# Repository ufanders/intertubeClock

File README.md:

# intertubeClock
An ESP32-powered nixie tube clock.
Power supply copied from this Hackaday.io project:
https://hackaday.io/project/27899-nixie-tube-power-supply

Read more about this project on my blog here!: https://www.andersknelson.com/blog/?p=363

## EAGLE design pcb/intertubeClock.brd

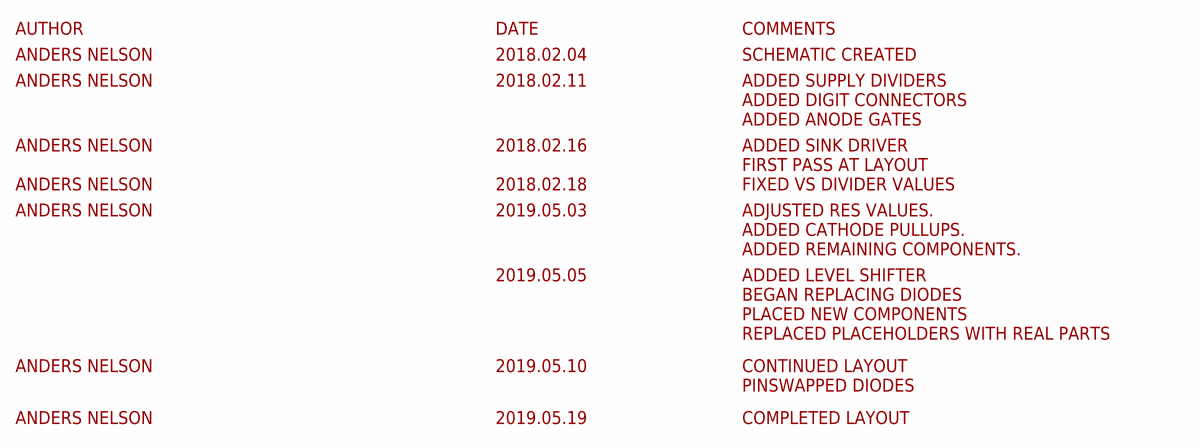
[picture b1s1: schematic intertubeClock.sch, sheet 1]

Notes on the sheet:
AUTHOR
DATE
COMMENTS
ANDERS NELSON
2018.02.04
SCHEMATIC CREATED
2018.02.11
ADDED SUPPLY DIVIDERS ADDED DIGIT CONNECTORS ADDED ANODE GATES
2018.02.16
ADDED SINK DRIVER FIRST PASS AT LAYOUT
FIXED VS DIVIDER VALUES
2019.05.03
2018.02.18
ADJUSTED RES VALUES. ADDED CATHODE PULLUPS. ADDED REMAINING COMPONENTS.
2019.05.05
ADDED LEVEL SHIFTER BEGAN REPLACING DIODES PLACED NEW COMPONENTS REPLACED PLACEHOLDERS WITH REAL PARTS
2019.05.10
CONTINUED LAYOUT PINSWAPPED DIODES
2019.05.19
COMPLETED LAYOUT

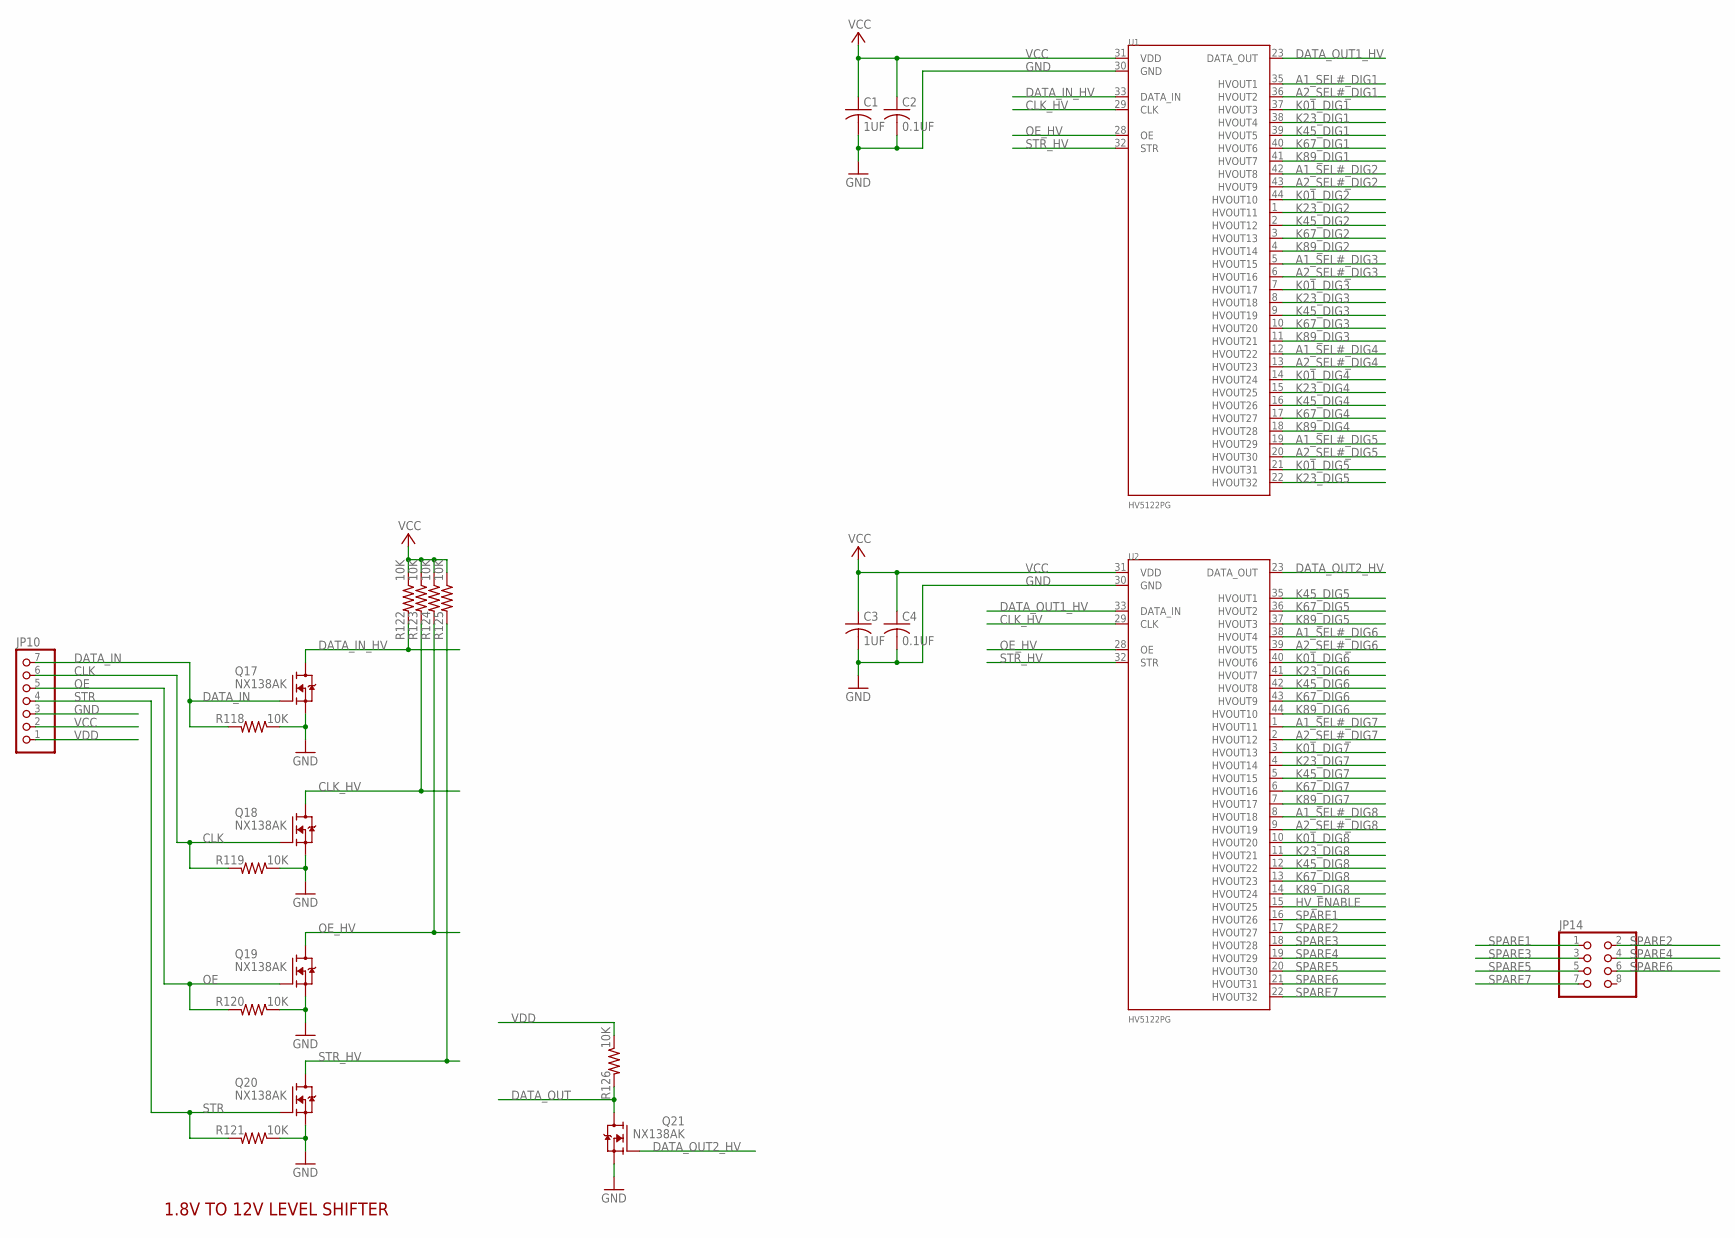
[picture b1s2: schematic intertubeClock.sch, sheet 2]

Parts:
C1, C3: 1UF; C0805
C2, C4: 0.1UF; C0805
JP10: PINHD-1X7; 1X07
JP14: PINHD-2X4; 2X04
Q17, Q18, Q19, Q20, Q21: NX138AK; SOT23
R118, R119, R120, R121, R122, R123, R124, R125, R126: 10K; R0603
U1, U2: HV5122PG; TQFP44

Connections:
A1_SEL#_DIG1: U1.35 (HVOUT1); also elsewhere on the board
A1_SEL#_DIG2: U1.42 (HVOUT8); also elsewhere on the board
A1_SEL#_DIG3: U1.5 (HVOUT15); also elsewhere on the board
A1_SEL#_DIG4: U1.12 (HVOUT22); also elsewhere on the board
A1_SEL#_DIG5: U1.19 (HVOUT29); also elsewhere on the board
A1_SEL#_DIG6: U2.38 (HVOUT4); also elsewhere on the board
A1_SEL#_DIG7: U2.1 (HVOUT11); also elsewhere on the board
A1_SEL#_DIG8: U2.8 (HVOUT18); also elsewhere on the board
A2_SEL#_DIG1: U1.36 (HVOUT2); also elsewhere on the board
A2_SEL#_DIG2: U1.43 (HVOUT9); also elsewhere on the board
A2_SEL#_DIG3: U1.6 (HVOUT16); also elsewhere on the board
A2_SEL#_DIG4: U1.13 (HVOUT23); also elsewhere on the board
A2_SEL#_DIG5: U1.20 (HVOUT30); also elsewhere on the board
A2_SEL#_DIG6: U2.39 (HVOUT5); also elsewhere on the board
A2_SEL#_DIG7: U2.2 (HVOUT12); also elsewhere on the board
A2_SEL#_DIG8: U2.9 (HVOUT19); also elsewhere on the board
CLK: JP10.6, Q18.1 (G), R119.2
CLK_HV: Q18.3 (D), R123.2, U1.29 (CLK), U2.29 (CLK)
DATA_IN: JP10.7, Q17.1 (G), R118.2
DATA_IN_HV: Q17.3 (D), R122.2, U1.33 (DATA_IN)
DATA_OUT: Q21.3 (D), R126.2
DATA_OUT1_HV: U1.23 (DATA_OUT), U2.33 (DATA_IN)
DATA_OUT2_HV: Q21.1 (G), U2.23 (DATA_OUT)
GND: C1.2, C2.2, C3.2, C4.2, JP10.3, Q17.2 (S), Q18.2 (S), Q19.2 (S), Q20.2 (S), Q21.2 (S), R118.1, R119.1, R120.1, R121.1, U1.30 (GND), U2.30 (GND); also elsewhere on the board
HV_ENABLE: U2.15 (HVOUT25)
K01_DIG1: U1.37 (HVOUT3); also elsewhere on the board
K01_DIG2: U1.44 (HVOUT10); also elsewhere on the board
K01_DIG3: U1.7 (HVOUT17); also elsewhere on the board
K01_DIG4: U1.14 (HVOUT24); also elsewhere on the board
K01_DIG5: U1.21 (HVOUT31); also elsewhere on the board
K01_DIG6: U2.40 (HVOUT6); also elsewhere on the board
K01_DIG7: U2.3 (HVOUT13); also elsewhere on the board
K01_DIG8: U2.10 (HVOUT20); also elsewhere on the board
K23_DIG1: U1.38 (HVOUT4); also elsewhere on the board
K23_DIG2: U1.1 (HVOUT11); also elsewhere on the board
K23_DIG3: U1.8 (HVOUT18); also elsewhere on the board
K23_DIG4: U1.15 (HVOUT25); also elsewhere on the board
K23_DIG5: U1.22 (HVOUT32); also elsewhere on the board
K23_DIG6: U2.41 (HVOUT7); also elsewhere on the board
K23_DIG7: U2.4 (HVOUT14); also elsewhere on the board
K23_DIG8: U2.11 (HVOUT21); also elsewhere on the board
K45_DIG1: U1.39 (HVOUT5); also elsewhere on the board
K45_DIG2: U1.2 (HVOUT12); also elsewhere on the board
K45_DIG3: U1.9 (HVOUT19); also elsewhere on the board
K45_DIG4: U1.16 (HVOUT26); also elsewhere on the board
K45_DIG5: U2.35 (HVOUT1); also elsewhere on the board
K45_DIG6: U2.42 (HVOUT8); also elsewhere on the board
K45_DIG7: U2.5 (HVOUT15); also elsewhere on the board
K45_DIG8: U2.12 (HVOUT22); also elsewhere on the board
K67_DIG1: U1.40 (HVOUT6); also elsewhere on the board
K67_DIG2: U1.3 (HVOUT13); also elsewhere on the board
K67_DIG3: U1.10 (HVOUT20); also elsewhere on the board
K67_DIG4: U1.17 (HVOUT27); also elsewhere on the board
K67_DIG5: U2.36 (HVOUT2); also elsewhere on the board
K67_DIG6: U2.43 (HVOUT9); also elsewhere on the board
K67_DIG7: U2.6 (HVOUT16); also elsewhere on the board
K67_DIG8: U2.13 (HVOUT23); also elsewhere on the board
K89_DIG1: U1.41 (HVOUT7); also elsewhere on the board
K89_DIG2: U1.4 (HVOUT14); also elsewhere on the board
K89_DIG3: U1.11 (HVOUT21); also elsewhere on the board
K89_DIG4: U1.18 (HVOUT28); also elsewhere on the board
K89_DIG5: U2.37 (HVOUT3); also elsewhere on the board
K89_DIG6: U2.44 (HVOUT10); also elsewhere on the board
K89_DIG7: U2.7 (HVOUT17); also elsewhere on the board
K89_DIG8: U2.14 (HVOUT24); also elsewhere on the board
OE: JP10.5, Q19.1 (G), R120.2
OE_HV: Q19.3 (D), R124.2, U1.28 (OE), U2.28 (OE)
SPARE1: JP14.1, U2.16 (HVOUT26)
SPARE2: JP14.2, U2.17 (HVOUT27)
SPARE3: JP14.3, U2.18 (HVOUT28)
SPARE4: JP14.4, U2.19 (HVOUT29)
SPARE5: JP14.5, U2.20 (HVOUT30)
SPARE6: JP14.6, U2.21 (HVOUT31)
SPARE7: JP14.7, U2.22 (HVOUT32)
STR: JP10.4, Q20.1 (G), R121.2
STR_HV: Q20.3 (D), R125.2, U1.32 (STR), U2.32 (STR)
VCC: C1.1, C2.1, C3.1, C4.1, JP10.2, R122.1, R123.1, R124.1, R125.1, U1.31 (VDD), U2.31 (VDD)
VDD: JP10.1, R126.1

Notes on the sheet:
1.8V TO 12V LEVEL SHIFTER

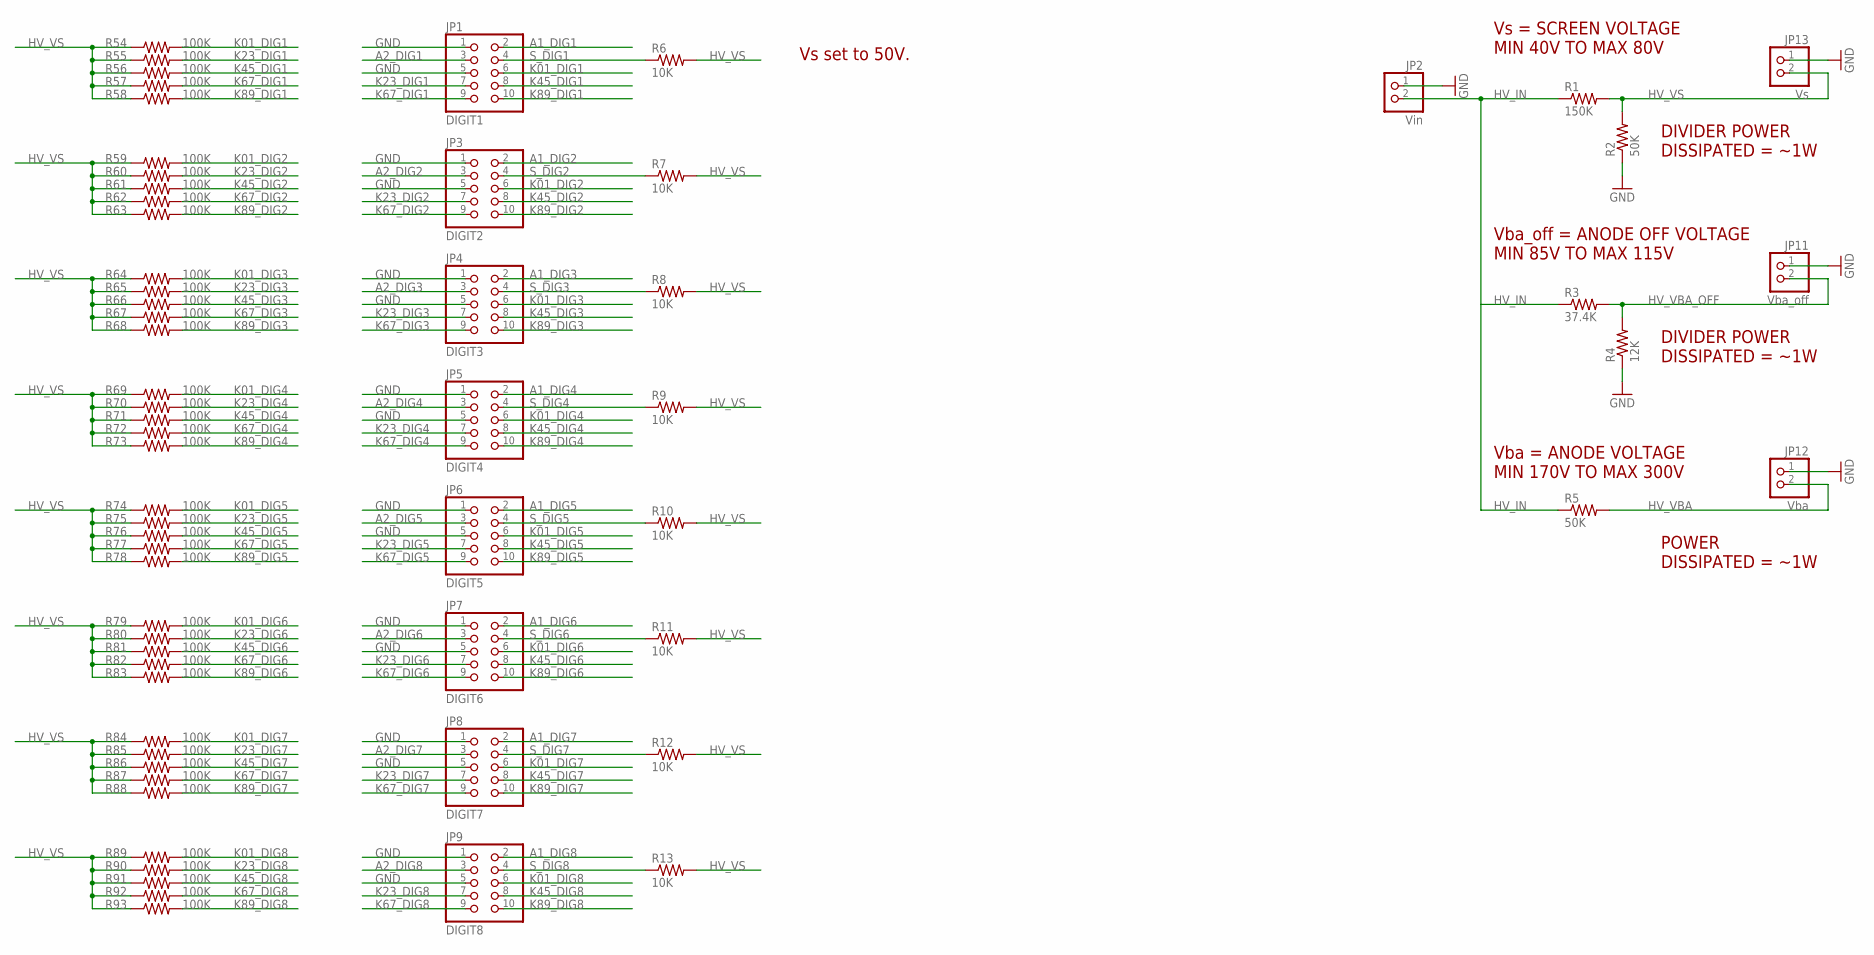
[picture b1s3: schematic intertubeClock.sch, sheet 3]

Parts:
JP1: DIGIT1; 2X05
JP2: Vin; 1X02
JP3: DIGIT2; 2X05
JP4: DIGIT3; 2X05
JP5: DIGIT4; 2X05
JP6: DIGIT5; 2X05
JP7: DIGIT6; 2X05
JP8: DIGIT7; 2X05
JP9: DIGIT8; 2X05
JP11: Vba_off; 1X02
JP12: Vba; 1X02
JP13: Vs; 1X02
R1: 150K; R2512
R2, R5: 50K; R2512
R3: 37.4K; R2512
R4: 12K; R2512
R6, R7, R8, R9, R10, R11, R12, R13: 10K; R1206
R54, R55, R56, R57, R58, R59, R60, R61, R62, R63, R64, R65, R66, R67, R68, R69, R70, R71, R72, R73, R74, R75, R76, R77, R78, R79, R80, R81, R82, R83, R84, R85, R86, R87, R88, R89, R90, R91, R92, R93: 100K; R1206

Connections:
A1_DIG1: JP1.2; also elsewhere on the board
A1_DIG2: JP3.2; also elsewhere on the board
A1_DIG3: JP4.2; also elsewhere on the board
A1_DIG4: JP5.2; also elsewhere on the board
A1_DIG5: JP6.2; also elsewhere on the board
A1_DIG6: JP7.2; also elsewhere on the board
A1_DIG7: JP8.2; also elsewhere on the board
A1_DIG8: JP9.2; also elsewhere on the board
A2_DIG1: JP1.3; also elsewhere on the board
A2_DIG2: JP3.3; also elsewhere on the board
A2_DIG3: JP4.3; also elsewhere on the board
A2_DIG4: JP5.3; also elsewhere on the board
A2_DIG5: JP6.3; also elsewhere on the board
A2_DIG6: JP7.3; also elsewhere on the board
A2_DIG7: JP8.3; also elsewhere on the board
A2_DIG8: JP9.3; also elsewhere on the board
GND: JP1.1, JP1.5, JP2.1, JP3.1, JP3.5, JP4.1, JP4.5, JP5.1, JP5.5, JP6.1, JP6.5, JP7.1, JP7.5, JP8.1, JP8.5, JP9.1, JP9.5, JP11.1, JP12.1, JP13.1, R2.1, R4.1; also elsewhere on the board
HV_IN: JP2.2, R1.1, R3.1, R5.1
HV_VBA: JP12.2, R5.2; also elsewhere on the board
HV_VBA_OFF: JP11.2, R3.2, R4.2; also elsewhere on the board
HV_VS: JP13.2, R1.2, R2.2, R6.2, R7.2, R8.2, R9.2, R10.2, R11.2, R12.2, R13.2, R54.1, R55.1, R56.1, R57.1, R58.1, R59.1, R60.1, R61.1, R62.1, R63.1, R64.1, R65.1, R66.1, R67.1, R68.1, R69.1, R70.1, R71.1, R72.1, R73.1, R74.1, R75.1, R76.1, R77.1, R78.1, R79.1, R80.1, R81.1, R82.1, R83.1, R84.1, R85.1, R86.1, R87.1, R88.1, R89.1, R90.1, R91.1, R92.1, R93.1
K01_DIG1: JP1.6, R54.2; also elsewhere on the board
K01_DIG2: JP3.6, R59.2; also elsewhere on the board
K01_DIG3: JP4.6, R64.2; also elsewhere on the board
K01_DIG4: JP5.6, R69.2; also elsewhere on the board
K01_DIG5: JP6.6, R74.2; also elsewhere on the board
K01_DIG6: JP7.6, R79.2; also elsewhere on the board
K01_DIG7: JP8.6, R84.2; also elsewhere on the board
K01_DIG8: JP9.6, R89.2; also elsewhere on the board
K23_DIG1: JP1.7, R55.2; also elsewhere on the board
K23_DIG2: JP3.7, R60.2; also elsewhere on the board
K23_DIG3: JP4.7, R65.2; also elsewhere on the board
K23_DIG4: JP5.7, R70.2; also elsewhere on the board
K23_DIG5: JP6.7, R75.2; also elsewhere on the board
K23_DIG6: JP7.7, R80.2; also elsewhere on the board
K23_DIG7: JP8.7, R85.2; also elsewhere on the board
K23_DIG8: JP9.7, R90.2; also elsewhere on the board
K45_DIG1: JP1.8, R56.2; also elsewhere on the board
K45_DIG2: JP3.8, R61.2; also elsewhere on the board
K45_DIG3: JP4.8, R66.2; also elsewhere on the board
K45_DIG4: JP5.8, R71.2; also elsewhere on the board
K45_DIG5: JP6.8, R76.2; also elsewhere on the board
K45_DIG6: JP7.8, R81.2; also elsewhere on the board
K45_DIG7: JP8.8, R86.2; also elsewhere on the board
K45_DIG8: JP9.8, R91.2; also elsewhere on the board
K67_DIG1: JP1.9, R57.2; also elsewhere on the board
K67_DIG2: JP3.9, R62.2; also elsewhere on the board
K67_DIG3: JP4.9, R67.2; also elsewhere on the board
K67_DIG4: JP5.9, R72.2; also elsewhere on the board
K67_DIG5: JP6.9, R77.2; also elsewhere on the board
K67_DIG6: JP7.9, R82.2; also elsewhere on the board
K67_DIG7: JP8.9, R87.2; also elsewhere on the board
K67_DIG8: JP9.9, R92.2; also elsewhere on the board
K89_DIG1: JP1.10, R58.2; also elsewhere on the board
K89_DIG2: JP3.10, R63.2; also elsewhere on the board
K89_DIG3: JP4.10, R68.2; also elsewhere on the board
K89_DIG4: JP5.10, R73.2; also elsewhere on the board
K89_DIG5: JP6.10, R78.2; also elsewhere on the board
K89_DIG6: JP7.10, R83.2; also elsewhere on the board
K89_DIG7: JP8.10, R88.2; also elsewhere on the board
K89_DIG8: JP9.10, R93.2; also elsewhere on the board
S_DIG1: JP1.4, R6.1
S_DIG2: JP3.4, R7.1
S_DIG3: JP4.4, R8.1
S_DIG4: JP5.4, R9.1
S_DIG5: JP6.4, R10.1
S_DIG6: JP7.4, R11.1
S_DIG7: JP8.4, R12.1
S_DIG8: JP9.4, R13.1

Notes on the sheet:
Vs = SCREEN VOLTAGE MIN 40V TO MAX 80V
DIVIDER POWER DISSIPATED = ~1W
Vba_off = ANODE OFF VOLTAGE MIN 85V TO MAX 115V
Vba = ANODE VOLTAGE MIN 170V TO MAX 300V
POWER DISSIPATED = ~1W
Vs set to 50V.

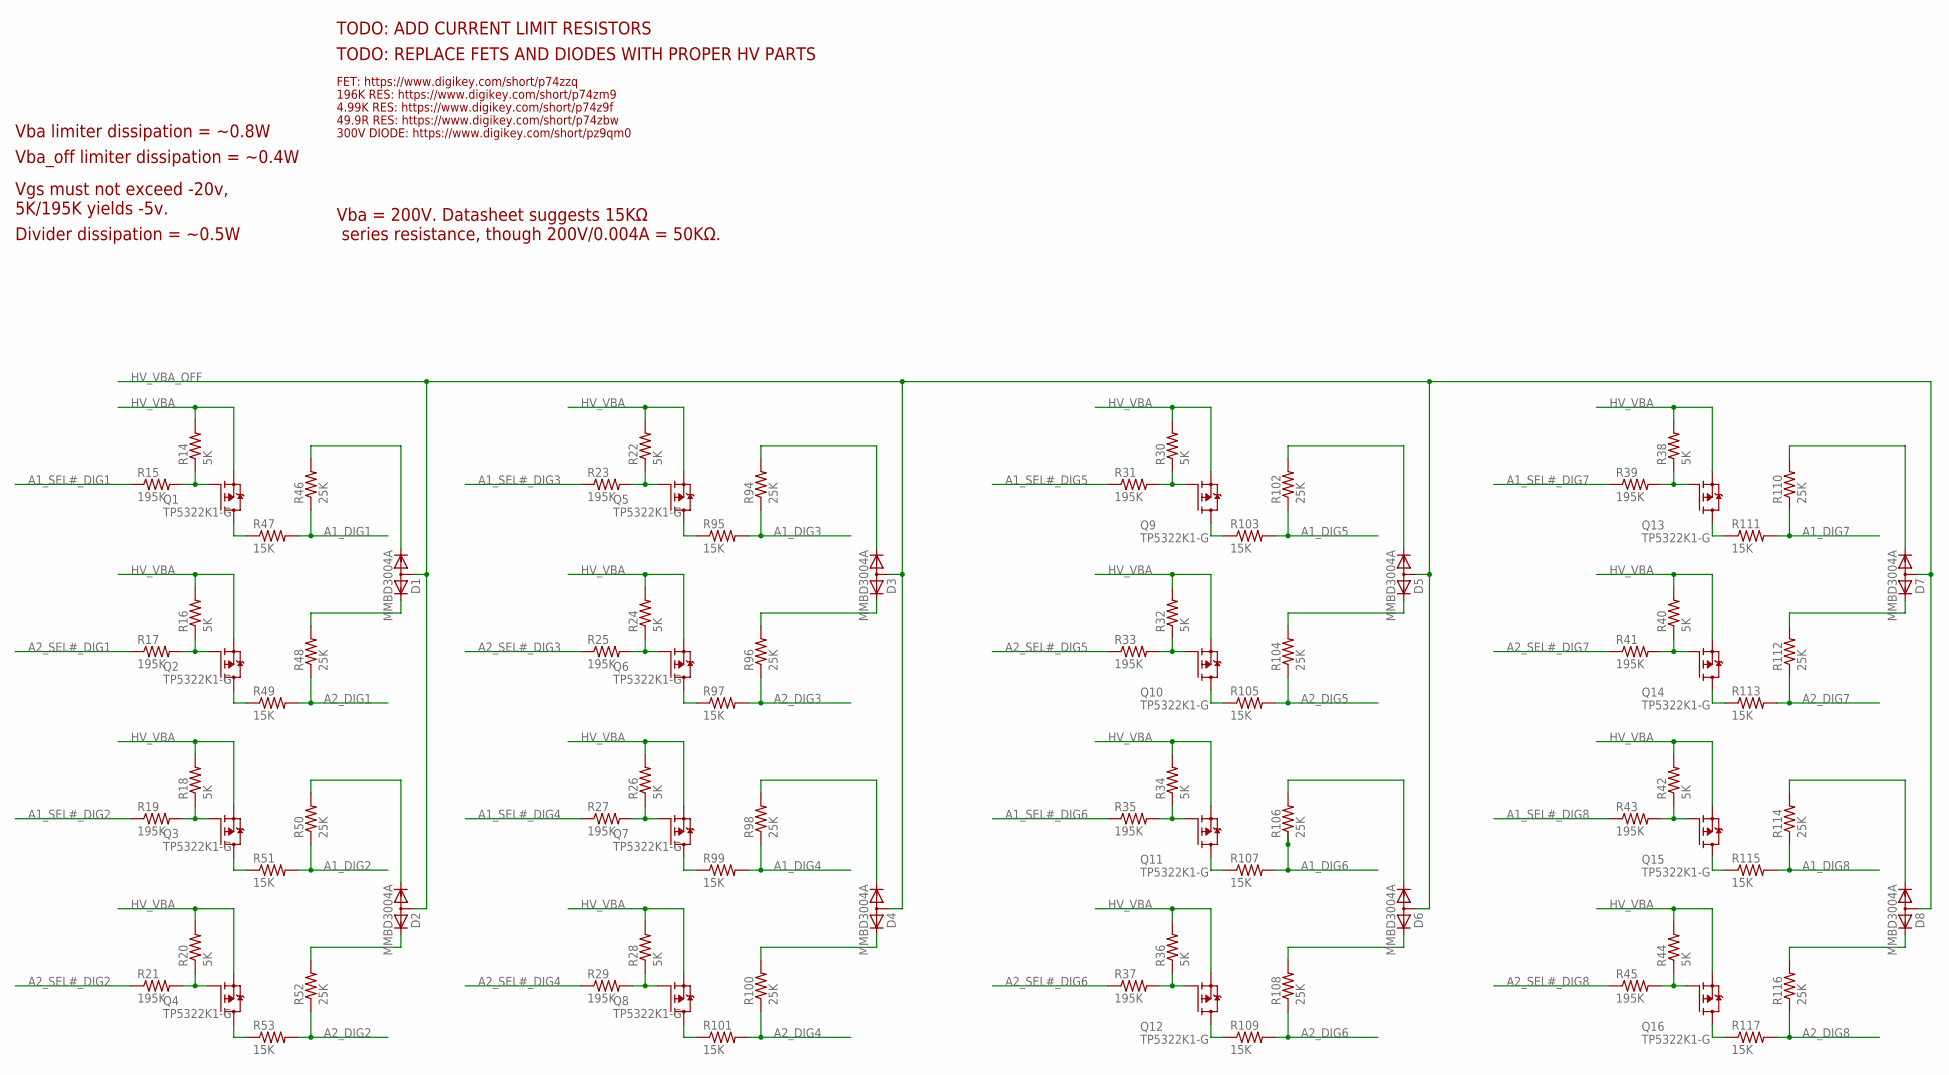
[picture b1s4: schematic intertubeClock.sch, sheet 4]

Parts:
D1, D2, D3, D4, D5, D6, D7, D8: MMBD3004A; SOT23
Q1, Q2, Q3, Q4, Q5, Q6, Q7, Q8, Q9, Q10, Q11, Q12, Q13, Q14, Q15, Q16: TP5322K1-G; SOT23
R14, R16, R18, R20, R22, R24, R26, R28, R30, R32, R34, R36, R38, R40, R42, R44: 5K; R1206
R15, R17, R19, R21, R23, R25, R27, R29, R31, R33, R35, R37, R39, R41, R43, R45: 195K; R1206
R46, R48, R50, R52, R94, R96, R98, R100, R102, R104, R106, R108, R110, R112, R114, R116: 25K; R1206
R47, R49, R51, R53, R95, R97, R99, R101, R103, R105, R107, R109, R111, R113, R115, R117: 15K; R1206

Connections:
A1_DIG1: R46.1, R47.2; also elsewhere on the board
A1_DIG2: R50.1, R51.2; also elsewhere on the board
A1_DIG3: R94.1, R95.2; also elsewhere on the board
A1_DIG4: R98.1, R99.2; also elsewhere on the board
A1_DIG5: R102.1, R103.2; also elsewhere on the board
A1_DIG6: R106.1, R107.2; also elsewhere on the board
A1_DIG7: R110.1, R111.2; also elsewhere on the board
A1_DIG8: R114.1, R115.2; also elsewhere on the board
A1_SEL#_DIG1: R15.1; also elsewhere on the board
A1_SEL#_DIG2: R19.1; also elsewhere on the board
A1_SEL#_DIG3: R23.1; also elsewhere on the board
A1_SEL#_DIG4: R27.1; also elsewhere on the board
A1_SEL#_DIG5: R31.1; also elsewhere on the board
A1_SEL#_DIG6: R35.1; also elsewhere on the board
A1_SEL#_DIG7: R39.1; also elsewhere on the board
A1_SEL#_DIG8: R43.1; also elsewhere on the board
A2_DIG1: R48.1, R49.2; also elsewhere on the board
A2_DIG2: R52.1, R53.2; also elsewhere on the board
A2_DIG3: R96.1, R97.2; also elsewhere on the board
A2_DIG4: R100.1, R101.2; also elsewhere on the board
A2_DIG5: R104.1, R105.2; also elsewhere on the board
A2_DIG6: R108.1, R109.2; also elsewhere on the board
A2_DIG7: R112.1, R113.2; also elsewhere on the board
A2_DIG8: R116.1, R117.2; also elsewhere on the board
A2_SEL#_DIG1: R17.1; also elsewhere on the board
A2_SEL#_DIG2: R21.1; also elsewhere on the board
A2_SEL#_DIG3: R25.1; also elsewhere on the board
A2_SEL#_DIG4: R29.1; also elsewhere on the board
A2_SEL#_DIG5: R33.1; also elsewhere on the board
A2_SEL#_DIG6: R37.1; also elsewhere on the board
A2_SEL#_DIG7: R41.1; also elsewhere on the board
A2_SEL#_DIG8: R45.1; also elsewhere on the board
HV_VBA: Q1.2 (S), Q2.2 (S), Q3.2 (S), Q4.2 (S), Q5.2 (S), Q6.2 (S), Q7.2 (S), Q8.2 (S), Q9.2 (S), Q10.2 (S), Q11.2 (S), Q12.2 (S), Q13.2 (S), Q14.2 (S), Q15.2 (S), Q16.2 (S), R14.2, R16.2, R18.2, R20.2, R22.2, R24.2, R26.2, R28.2, R30.2, R32.2, R34.2, R36.2, R38.2, R40.2, R42.2, R44.2; also elsewhere on the board
HV_VBA_OFF: D1.3 (A), D2.3 (A), D3.3 (A), D4.3 (A), D5.3 (A), D6.3 (A), D7.3 (A), D8.3 (A); also elsewhere on the board
unnamed: Q1.1 (G), R14.1, R15.2
unnamed: Q2.1 (G), R16.1, R17.2
unnamed: Q3.1 (G), R18.1, R19.2
unnamed: Q4.1 (G), R20.1, R21.2
unnamed: Q5.1 (G), R22.1, R23.2
unnamed: Q6.1 (G), R24.1, R25.2
unnamed: Q7.1 (G), R26.1, R27.2
unnamed: Q8.1 (G), R28.1, R29.2
unnamed: Q9.1 (G), R30.1, R31.2
unnamed: Q10.1 (G), R32.1, R33.2
unnamed: Q11.1 (G), R34.1, R35.2
unnamed: Q12.1 (G), R36.1, R37.2
unnamed: Q13.1 (G), R38.1, R39.2
unnamed: Q14.1 (G), R40.1, R41.2
unnamed: Q15.1 (G), R42.1, R43.2
unnamed: Q16.1 (G), R44.1, R45.2
unnamed: Q1.3 (D), R47.1
unnamed: D1.1 (K1), R46.2
unnamed: Q2.3 (D), R49.1
unnamed: D1.2 (K2), R48.2
unnamed: Q3.3 (D), R51.1
unnamed: D2.1 (K1), R50.2
unnamed: Q4.3 (D), R53.1
unnamed: D2.2 (K2), R52.2
unnamed: D3.1 (K1), R94.2
unnamed: D3.2 (K2), R96.2
unnamed: D4.1 (K1), R98.2
unnamed: D4.2 (K2), R100.2
unnamed: Q9.3 (D), R103.1
unnamed: D5.1 (K1), R102.2
unnamed: D5.2 (K2), R104.2
unnamed: D6.1 (K1), R106.2
unnamed: D6.2 (K2), R108.2
unnamed: Q13.3 (D), R111.1
unnamed: D7.1 (K1), R110.2
unnamed: D7.2 (K2), R112.2
unnamed: D8.1 (K1), R114.2
unnamed: D8.2 (K2), R116.2
unnamed: Q5.3 (D), R95.1
unnamed: Q6.3 (D), R97.1
unnamed: Q7.3 (D), R99.1
unnamed: Q8.3 (D), R101.1
unnamed: Q10.3 (D), R105.1
unnamed: Q11.3 (D), R107.1
unnamed: Q12.3 (D), R109.1
unnamed: Q14.3 (D), R113.1
unnamed: Q15.3 (D), R115.1
unnamed: Q16.3 (D), R117.1

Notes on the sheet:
Vgs must not exceed -20v, 5K/195K yields -5v.
Divider dissipation = ~0.5W
TODO: ADD CURRENT LIMIT RESISTORS
TODO: REPLACE FETS AND DIODES WITH PROPER HV PARTS
Vba limiter dissipation = ~0.8W
Vba_off limiter dissipation = ~0.4W
FET: https://www.digikey.com/short/p74zzq
196K RES: https://www.digikey.com/short/p74zm9
4.99K RES: https://www.digikey.com/short/p74z9f
49.9R RES: https://www.digikey.com/short/p74zbw
Vba = 200V. Datasheet suggests 15KΩ series resistance, though 200V/0.004A = 50KΩ.
300V DIODE: https://www.digikey.com/short/pz9qm0

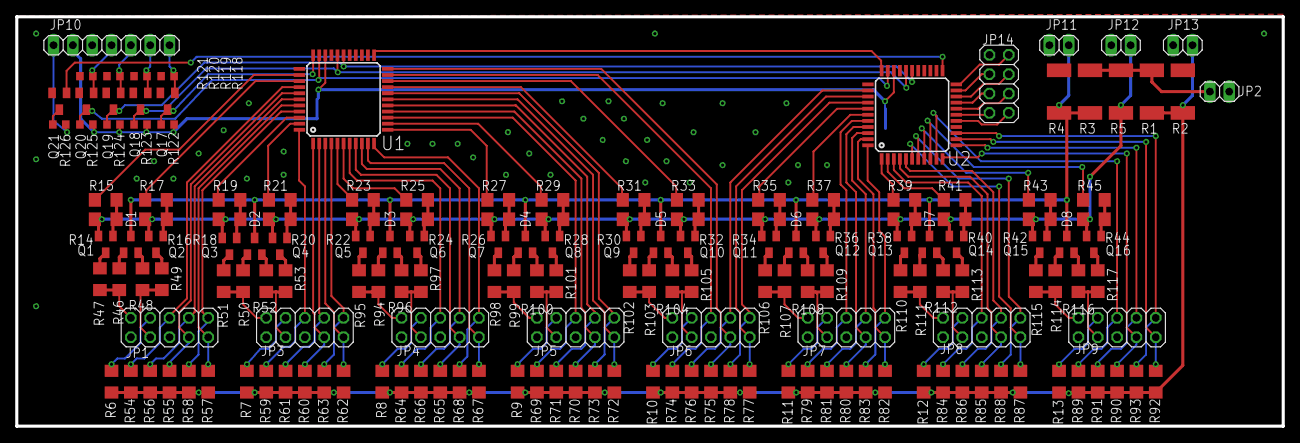
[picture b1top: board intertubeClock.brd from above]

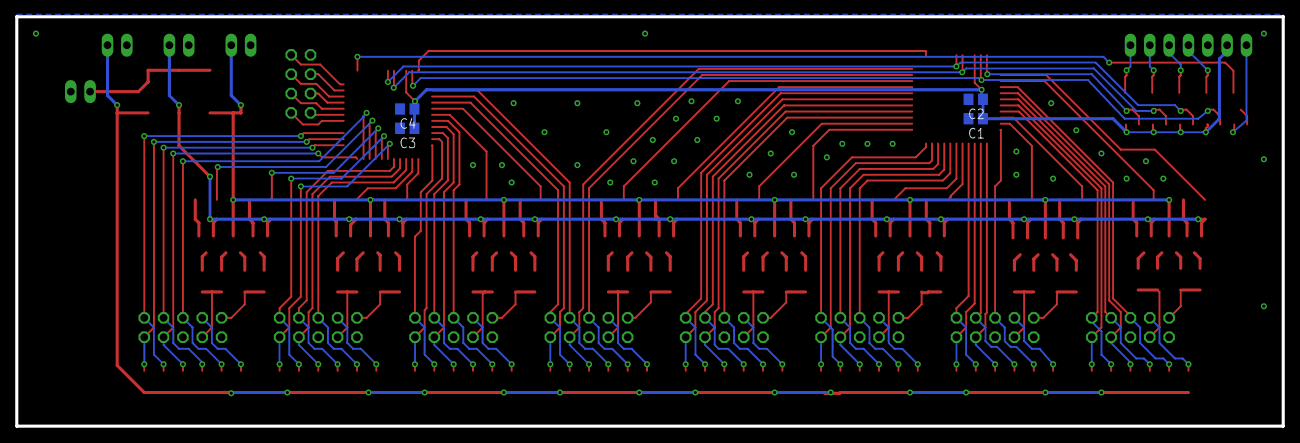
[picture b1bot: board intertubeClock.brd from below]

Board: 2 copper layers, 166.3 x 53.8 mm, 175 parts (4 on the bottom side), 153 nets.

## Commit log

2018-02-11 -Schematic created.
2018-02-18 -ADDED SINK DRIVER -ADDED GATES AND DIVIDERS -FIRST PASS AT LAYOUT
2018-05-22 -Added power supply items. -Fixed anode nets. -Adjusted resistor packages.
2019-05-04 -Fixed voltage divider values. -Added diodes.
2019-05-04 -Added remaining components.
2019-05-05 -ADDED LEVEL SHIFTER -BEGAN REPLACING DIODES
2019-05-05 -PLACED NEW COMPONENTS.
2019-05-06 -More layout work. -Added real parts library.
2019-05-11 -Continued layout. -Pinswapped diodes.
2019-05-12 -Continued layout.
2019-05-20 -Completed layout.
2019-07-01 -Tweaked silkscreen.
2022-09-01 -gitignoring EAGLE backups.
